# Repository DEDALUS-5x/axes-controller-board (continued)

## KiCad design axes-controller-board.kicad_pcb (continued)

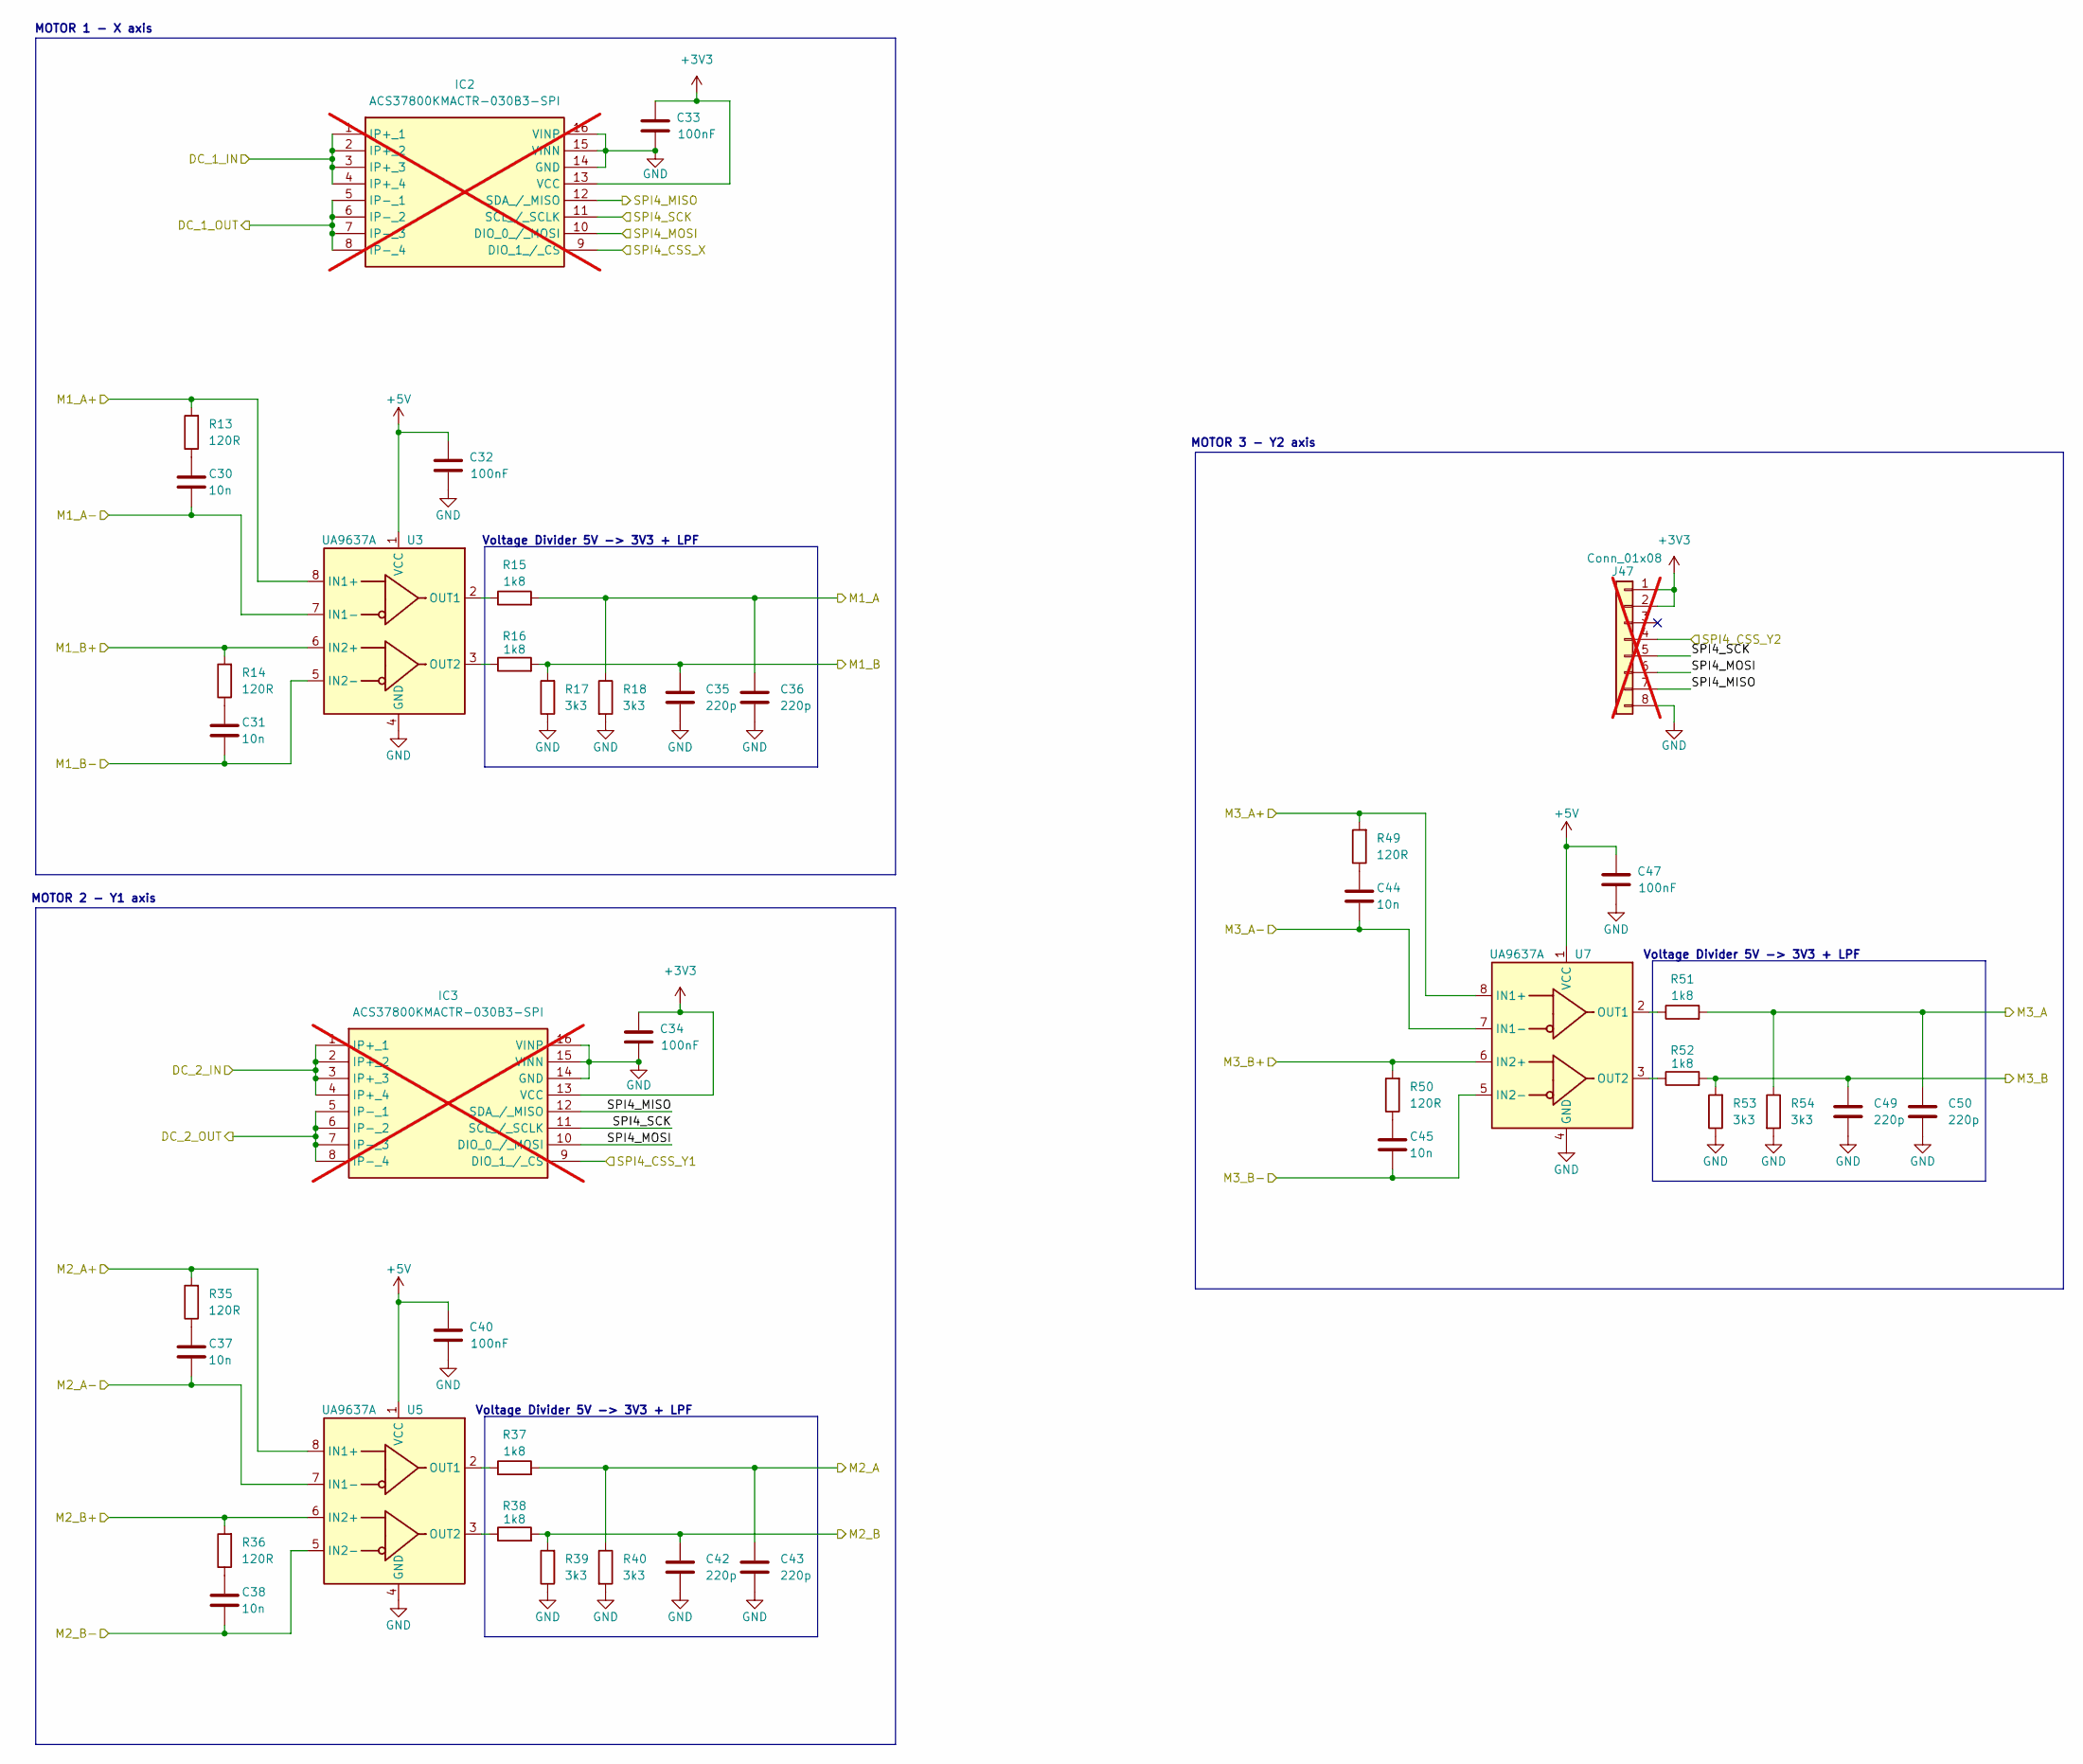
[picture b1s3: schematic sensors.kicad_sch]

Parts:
C30, C31, C37, C38, C44, C45: 10n; C_0603_1608Metric; LCSC C57112
C32, C33, C34, C40, C47: 100nF; C_0603_1608Metric; LCSC C14663
C35, C36, C42, C43, C49, C50: 220p; C_0603_1608Metric; LCSC C1603
IC2, IC3: ACS37800KMACTR-030B3-SPI; SOIC127P1030X265-16N; Mouser Part Number 250-KMACTR-030B3-SPI; not fitted
J47: Conn_01x08; PinHeader_1x08_P2.54mm_Vertical; not fitted
R13, R14, R35, R36, R49, R50: 120R; R_0603_1608Metric; LCSC C22787
R15, R16, R37, R38, R51, R52: 1k8; R_0603_1608Metric; LCSC C4177
R17, R18, R39, R40, R53, R54: 3k3; R_0603_1608Metric; LCSC C22978
U3, U5, U7: UA9637A; SOIC-8_3.9x4.9mm_P1.27mm; LCSC C434452

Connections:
+3V3: C33.1, C34.1, IC2.13 (VCC), IC3.13 (VCC), J47.1, J47.2; also elsewhere on the board
+5V: C32.1, C40.1, C47.1, U3.1 (VCC), U5.1 (VCC), U7.1 (VCC); also elsewhere on the board
/MCU/MX_A: C36.1, R15.2, R18.1; also elsewhere on the board
/MCU/MX_B: C35.1, R16.2, R17.2; also elsewhere on the board
/MCU/MY1_A: C43.1, R37.2, R40.1; also elsewhere on the board
/MCU/MY1_B: C42.1, R38.2, R39.2; also elsewhere on the board
/MCU/MY2_A: C50.1, R51.2, R54.1; also elsewhere on the board
/MCU/MY2_B: C49.1, R52.2, R53.2; also elsewhere on the board
/MCU/SPI4_CSS_X: IC2.9 (DIO_1_/_CS); also elsewhere on the board
/MCU/SPI4_CSS_Y1: IC3.9 (DIO_1_/_CS); also elsewhere on the board
/MCU/SPI4_CSS_Y2: J47.4; also elsewhere on the board
/Sensors/DC_1_IN: IC2.1 (IP+_1), IC2.2 (IP+_2), IC2.3 (IP+_3), IC2.4 (IP+_4); also elsewhere on the board
/Sensors/DC_1_OUT: IC2.5 (IP-_1), IC2.6 (IP-_2), IC2.7 (IP-_3), IC2.8 (IP-_4); also elsewhere on the board
/Sensors/DC_2_IN: IC3.1 (IP+_1), IC3.2 (IP+_2), IC3.3 (IP+_3), IC3.4 (IP+_4); also elsewhere on the board
/Sensors/DC_2_OUT: IC3.5 (IP-_1), IC3.6 (IP-_2), IC3.7 (IP-_3), IC3.8 (IP-_4); also elsewhere on the board
/Sensors/M1_A+: R13.2, U3.8 (IN1+); also elsewhere on the board
/Sensors/M1_A-: C30.2, U3.7 (IN1-); also elsewhere on the board
/Sensors/M1_B+: R14.2, U3.6 (IN2+); also elsewhere on the board
/Sensors/M1_B-: C31.2, U3.5 (IN2-); also elsewhere on the board
/Sensors/M2_A+: R35.2, U5.8 (IN1+); also elsewhere on the board
/Sensors/M2_A-: C37.2, U5.7 (IN1-); also elsewhere on the board
/Sensors/M2_B+: R36.2, U5.6 (IN2+); also elsewhere on the board
/Sensors/M2_B-: C38.2, U5.5 (IN2-); also elsewhere on the board
/Sensors/M3_A+: R49.2, U7.8 (IN1+); also elsewhere on the board
/Sensors/M3_A-: C44.2, U7.7 (IN1-); also elsewhere on the board
/Sensors/M3_B+: R50.2, U7.6 (IN2+); also elsewhere on the board
/Sensors/M3_B-: C45.2, U7.5 (IN2-); also elsewhere on the board
/Sensors/SPI4_MISO: IC2.12 (SDA_/_MISO), IC3.12 (SDA_/_MISO), J47.7; also elsewhere on the board
/Sensors/SPI4_MOSI: IC2.10 (DIO_0_/_MOSI), IC3.10 (DIO_0_/_MOSI), J47.6; also elsewhere on the board
/Sensors/SPI4_SCK: IC2.11 (SCL_/_SCLK), IC3.11 (SCL_/_SCLK), J47.5; also elsewhere on the board
GND: C32.2, C33.2, C34.2, C35.2, C36.2, C40.2, C42.2, C43.2, C47.2, C49.2, C50.2, IC2.14 (GND), IC2.15 (VINN), IC2.16 (VINP), IC3.14 (GND), IC3.15 (VINN), IC3.16 (VINP), J47.8, R17.1, R18.2, R39.1, R40.2, R53.1, R54.2, U3.4 (GND), U5.4 (GND), U7.4 (GND); also elsewhere on the board
unnamed: C30.1, R13.1
unnamed: C31.1, R14.1
unnamed: C37.1, R35.1
unnamed: C38.1, R36.1
unnamed: C44.1, R49.1
unnamed: C45.1, R50.1
unnamed: R15.1, U3.2 (OUT1)
unnamed: R16.1, U3.3 (OUT2)
unnamed: R37.1, U5.2 (OUT1)
unnamed: R38.1, U5.3 (OUT2)
unnamed: R51.1, U7.2 (OUT1)
unnamed: R52.1, U7.3 (OUT2)

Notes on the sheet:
Voltage Divider 5V -> 3V3 + LPF
MOTOR 3 - Y2 axis
MOTOR 2 - Y1 axis
MOTOR 1 - X axis

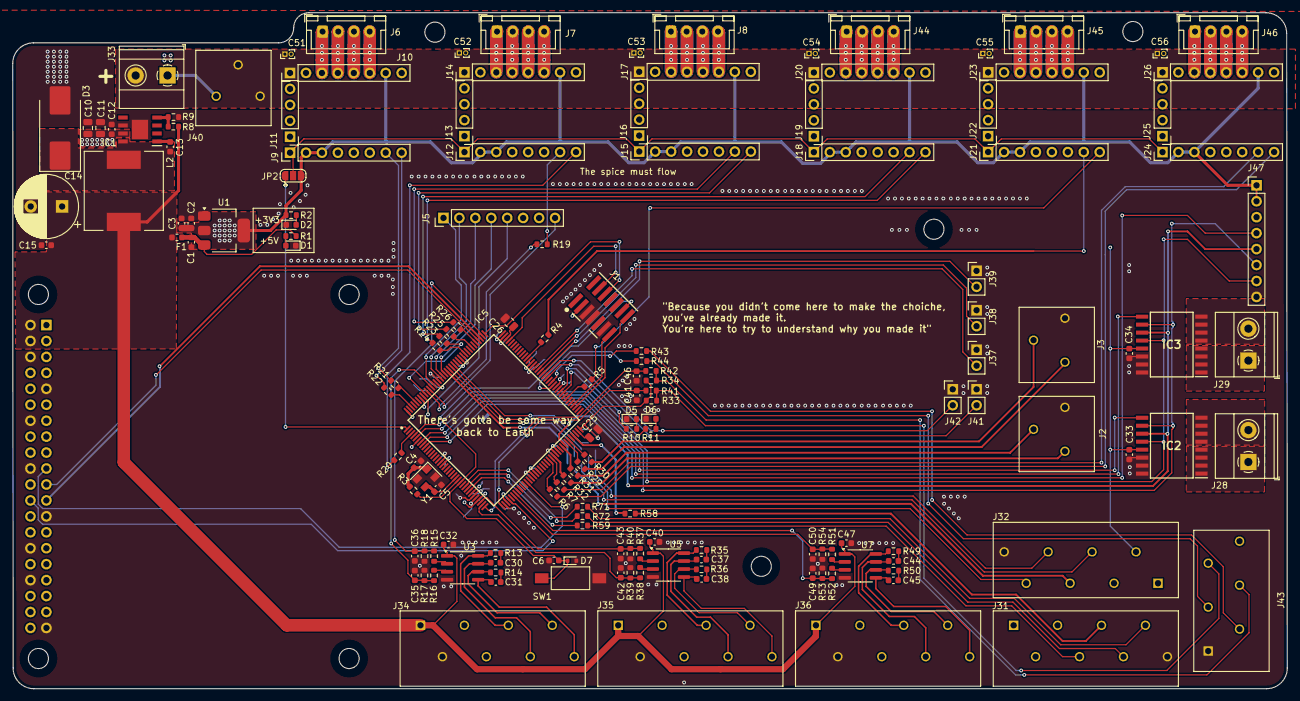
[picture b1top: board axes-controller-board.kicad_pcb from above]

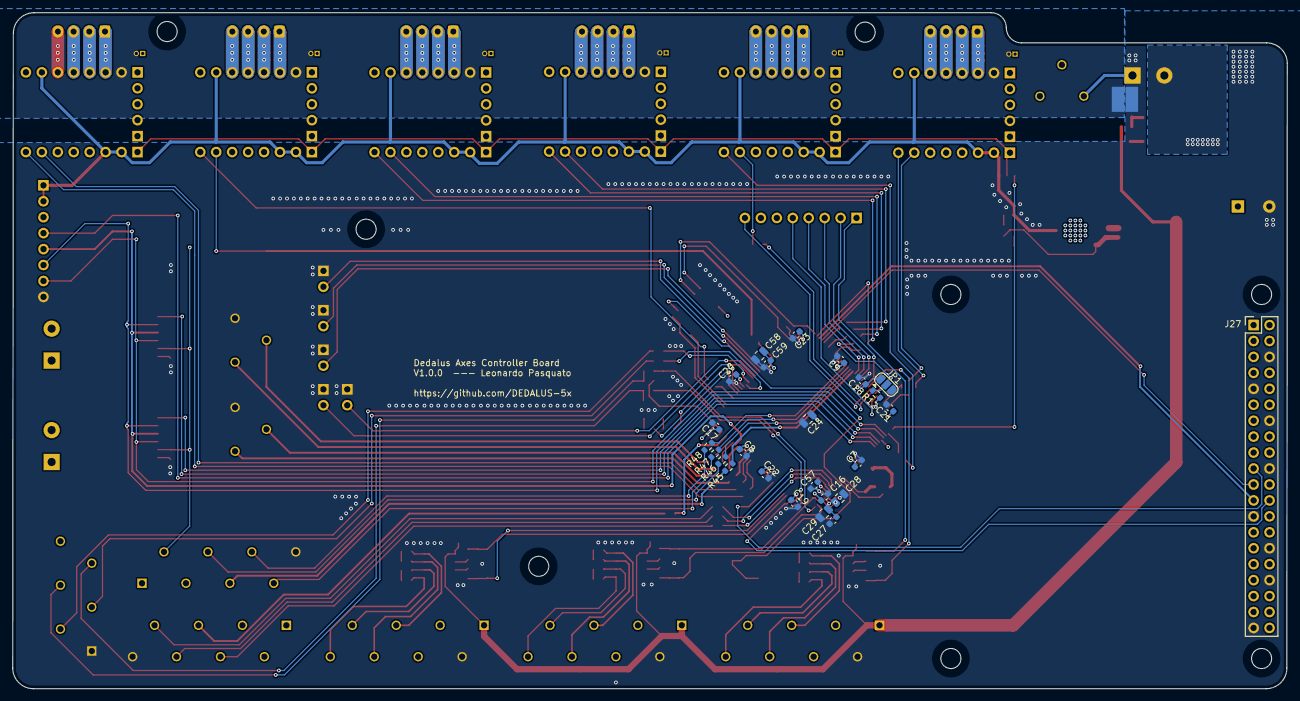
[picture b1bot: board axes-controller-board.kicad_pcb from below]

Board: 4 copper layers, 203.1 x 107.7 mm, 188 parts (25 on the bottom side), 164 nets.

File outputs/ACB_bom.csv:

"Reference","Value","Footprint","Qty","LCSC"
"C1,C2,C3","10u","Capacitor_SMD:C_0603_1608Metric","3","C19702"
"C4,C5","15pF","Capacitor_SMD:C_0603_1608Metric","2","C1644"
"C6,C32,C33,C34,C39,C40,C41,C46,C47","100nF","Capacitor_SMD:C_0603_1608Metric","9","C14663"
"C10,C11","4.7u","Capacitor_SMD:C_0805_2012Metric","2","C1779"
"C12,C13,C15,C30,C31,C37,C38,C44,C45","10n","Capacitor_SMD:C_0603_1608Metric","9","C57112"
"C25,C26","2.2u","Capacitor_SMD:C_0805_2012Metric","2","C377773"
"C35,C36,C42,C43,C49,C50","220p","Capacitor_SMD:C_0603_1608Metric","6","C1603"
"D1,D2","LED_Small","Diode_SMD:D_0603_1608Metric","2","C2286"
"D3","B540C","Diode_SMD:D_SMC_Handsoldering","1","C72264"
"D5,D6","LED_Small","LED_SMD:LED_0603_1608Metric","2","C2286"
"F1","750mA","Fuse:Fuse_0603_1608Metric","1","C206991"
"IC1","TPS5450QDDARQ1","Local:SOIC127P600X170-9N","1","C181270"
"IC5","STM32H723ZGT6","Local:QFP50P2200X2200X160-144N","1","C7089881"
"JP1","BOOT0","Jumper:SolderJumper-3_P1.3mm_Open_RoundedPad1.0x1.5mm","1",""
"L2","15u","Inductor_SMD:L_12x12mm_H6mm","1","C2847584"
"R1","2k","Resistor_SMD:R_0603_1608Metric","1","C22975"
"R2,R10,R11,R41,R42","1k","Resistor_SMD:R_0603_1608Metric","5","C21190"
"R3,R4,R5,R6,R7,R19,R20,R21,R22,R23,R24,R25,R26,R27,R28,R29,R30,R31,R32,R43,R44,R58,R59,R71,R72","33R","Resistor_SMD:R_0603_1608Metric","25","C23140"
"R8,R33,R34","10k","Resistor_SMD:R_0603_1608Metric","3","C25804"
"R9","3.16k","Resistor_SMD:R_0603_1608Metric","1","C100959"
"R13,R14,R35,R36,R49,R50","120R","Resistor_SMD:R_0603_1608Metric","6","C22787"
"R15,R16,R37,R38,R51,R52","1k8","Resistor_SMD:R_0603_1608Metric","6","C4177"
"R17,R18,R39,R40,R53,R54","3k3","Resistor_SMD:R_0603_1608Metric","6","C22978"
"U1","LM1117MP-3.3","Package_TO_SOT_SMD:SOT-223-3_TabPin2","1","C498153"
"U3,U5,U7","UA9637A","Package_SO:SOIC-8_3.9x4.9mm_P1.27mm","3","C434452"
"Y1","16MHz","Crystal:Crystal_SMD_EuroQuartz_MT-4Pin_3.2x2.5mm","1","C27869"

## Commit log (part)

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2026-01-24 feat: first schematic setup
2026-01-24 feat: 12 to 5V
2026-01-26 feat: setup hierarchy
2026-01-26 fix: 12V to 5V with TPS5450
    5V and 5A output, better choice for raspberry supply from it
2026-01-28 feat: microcontroller setup with decoupling caps
2026-02-01 feat: setup encoder reading
2026-02-02 feat: RC filter on encoder data
2026-02-03 feat: voltage divider on UA96 inputs from new llinear encoder
2026-02-03 feat: linear encoders for all 3 dc motors
2026-02-03 feat: setup heatbed and nozzle connectors
2026-02-05 feat: setup stepper circuitry
2026-02-06 fix: minors
2026-02-06 feat: pwm for dcs to micro, uart
2026-02-06 feat: setup spi
2026-02-07 feat: pwms for DC motors
2026-02-08 feat: raspberry spi dma setup and footprints fix
2026-02-09 fix: missing decoupling caps
2026-02-13 fix: no voltage divider is needed on encoders input
2026-02-13 feat: linear encoders connections
2026-02-13 feat: connection micro to stepper motors drivers
2026-02-20 fix: missing footprints and new current sensor
2026-02-20 feat: config spi4 for current sensors
2026-02-21 feat: rotative encoders connectors setup
2026-02-23 feat: current sensor setup
2026-02-23 fix: add indications
2026-02-23 fix: chip selects
2026-02-23 feat: setup micro on pcb
2026-02-23 feat: setup groups pcb
    steppers, micro, clock, current sensor - connector
2026-02-24 fix: missing input power connector
2026-02-24 feat: sbroglio encoders drivers
2026-02-24 feat: rasp, supply and micro setup on pcb, missing stepper motors connectors
2026-02-25 fix: dcdc layout according to datasheet
2026-02-25 feat: 3d models and first draft pcb edge cuts
2026-02-25 fix: connectors and pcb layout
2026-02-25 feat: gnd zones
2026-02-26 feat: endstops integration
2026-02-26 feat: spi and 3v3 routing
2026-02-26 fix: 33R resistors
2026-02-27 feat: spi4 connections
2026-02-27 feat: stepper motors connections to micro
2026-02-28 feat: dc driver connections
2026-02-28 fix: silkscreen
2026-02-28 feat: endstops connections
2026-03-02 fix: ground planes
2026-03-02 feat: nozzle and hb connections
2026-03-03 fix: nozzle and hb connector
2026-03-03 fix: 3d 6 pin connector libs, fix DRC
2026-03-03 feat: mounting holes
2026-03-03 feat: matrix cit
2026-03-03 feat: spare pins
2026-03-03 fix: spi sck wider traces and minors
2026-03-03 fix: gnd vias and comments
2026-03-03 fix: collision between encoder connector and raspberry aux
2026-03-03 fix: DNPs
2026-03-04 feat: production codes
2026-03-04 fix: remove bl decoupling caps from prod
2026-03-04 fix: root sheet LCSC codes
2026-03-04 feat: LCSC codes for all components to be soldered
2026-03-05 fix: prod notes
2026-03-05 fix: DNP for current sensors
2026-03-05 fix: 4.7 cap as basic
2026-03-05 feat: stepper connectors
2026-03-09 feat: 33R resistors on SPI1 and 2
2026-03-09 feat: stepper connections phases
2026-03-09 fix: missing traces
2026-03-19 fix: missing resistors
